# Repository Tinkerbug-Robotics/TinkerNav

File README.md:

# TinkerNav
RTK Rover and Base Station Firmware for TinkerNav Boards

For more information and boards go to: https://tinkerbugrobotics.com/

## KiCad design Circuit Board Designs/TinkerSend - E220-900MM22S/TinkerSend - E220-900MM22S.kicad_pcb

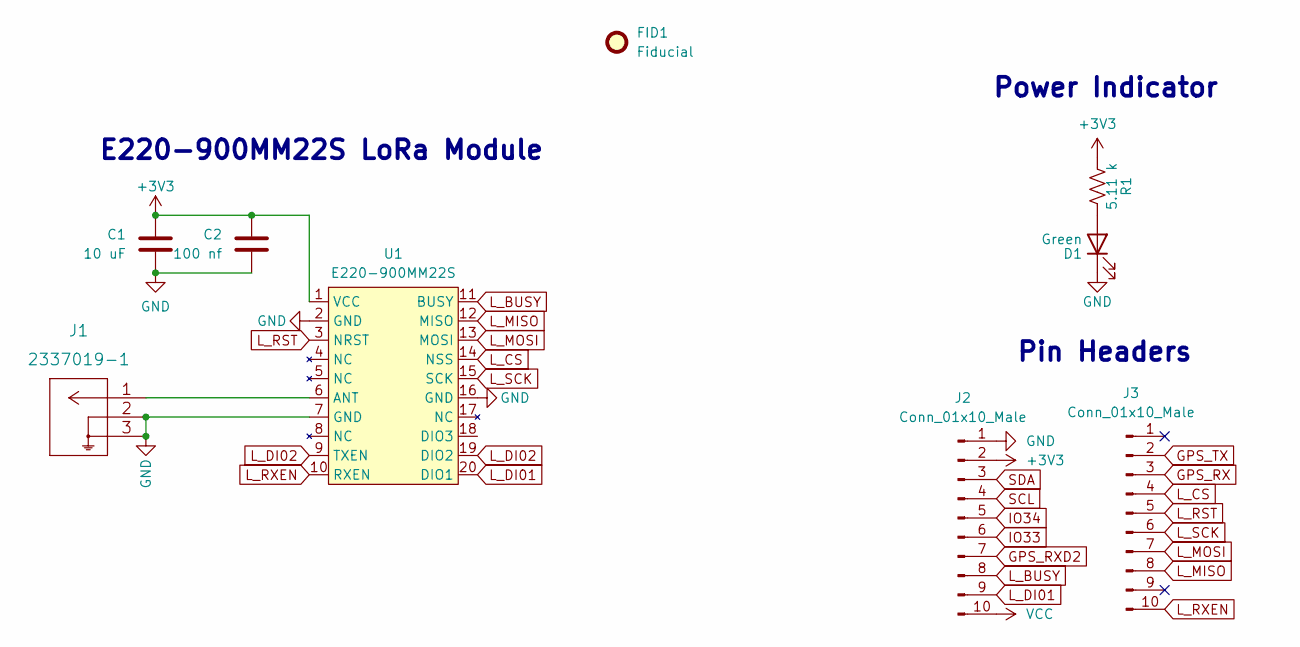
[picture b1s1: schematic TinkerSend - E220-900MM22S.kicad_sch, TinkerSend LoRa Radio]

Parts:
C1: 10 uF; C_0805_2012Metric
C2: 100 nf; C_0402_1005Metric
D1: Green; LED_0603_1608Metric
FID1: Fiducial; Fiducial_0.5mm_Mask1mm
J1: 2337019-1
J2, J3: Conn_01x10_Male; PinHeader_1x10_P2.54mm_Vertical
R1: 5.11 k; R_0603_1608Metric
U1: E220-900MM22S

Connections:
+3V3: C1.2, C2.2, J2.2, R1.2, U1.1 (VCC)
GND: C1.1, C2.1, D1.1 (K), J1.2, J1.3, J2.1, U1.2 (GND), U1.7 (GND), U1.16 (GND)
GPS_RX: J3.3
GPS_RXD2: J2.7
GPS_TX: J3.2
IO33: J2.6
IO34: J2.5
L_BUSY: J2.8, U1.11 (BUSY)
L_CS: J3.4, U1.14 (NSS)
L_DI01: J2.9, U1.20 (DIO1)
L_DI02: U1.9 (TXEN), U1.19 (DIO2)
L_MISO: J3.8, U1.12 (MISO)
L_MOSI: J3.7, U1.13 (MOSI)
L_RST: J3.5, U1.3 (NRST)
L_RXEN: J3.10, U1.10 (RXEN)
L_SCK: J3.6, U1.15 (SCK)
unnamed: D1.2 (A), R1.1
unnamed: J1.1, U1.6 (ANT)
SCL: J2.4
SDA: J2.3
VCC: J2.10

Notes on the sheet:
Power Indicator
Pin Headers
E220-900MM22S LoRa Module

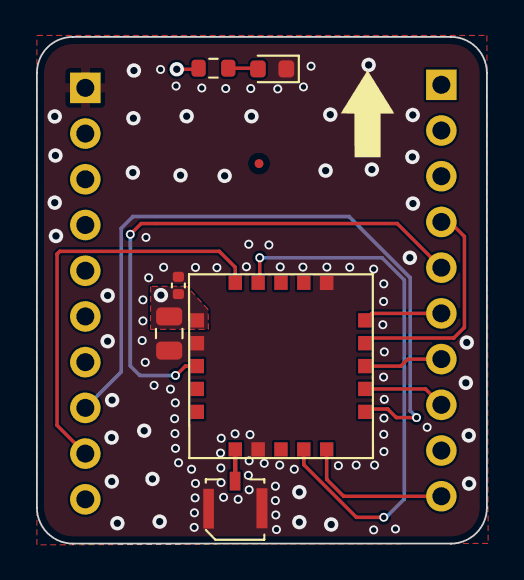
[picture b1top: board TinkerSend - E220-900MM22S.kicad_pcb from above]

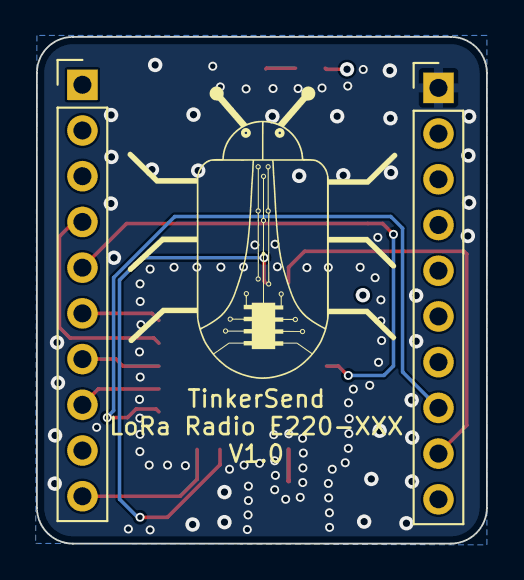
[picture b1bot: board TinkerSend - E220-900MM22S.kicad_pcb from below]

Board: 4 copper layers, 25.0 x 28.1 mm, 9 parts (2 on the bottom side), 13 nets.

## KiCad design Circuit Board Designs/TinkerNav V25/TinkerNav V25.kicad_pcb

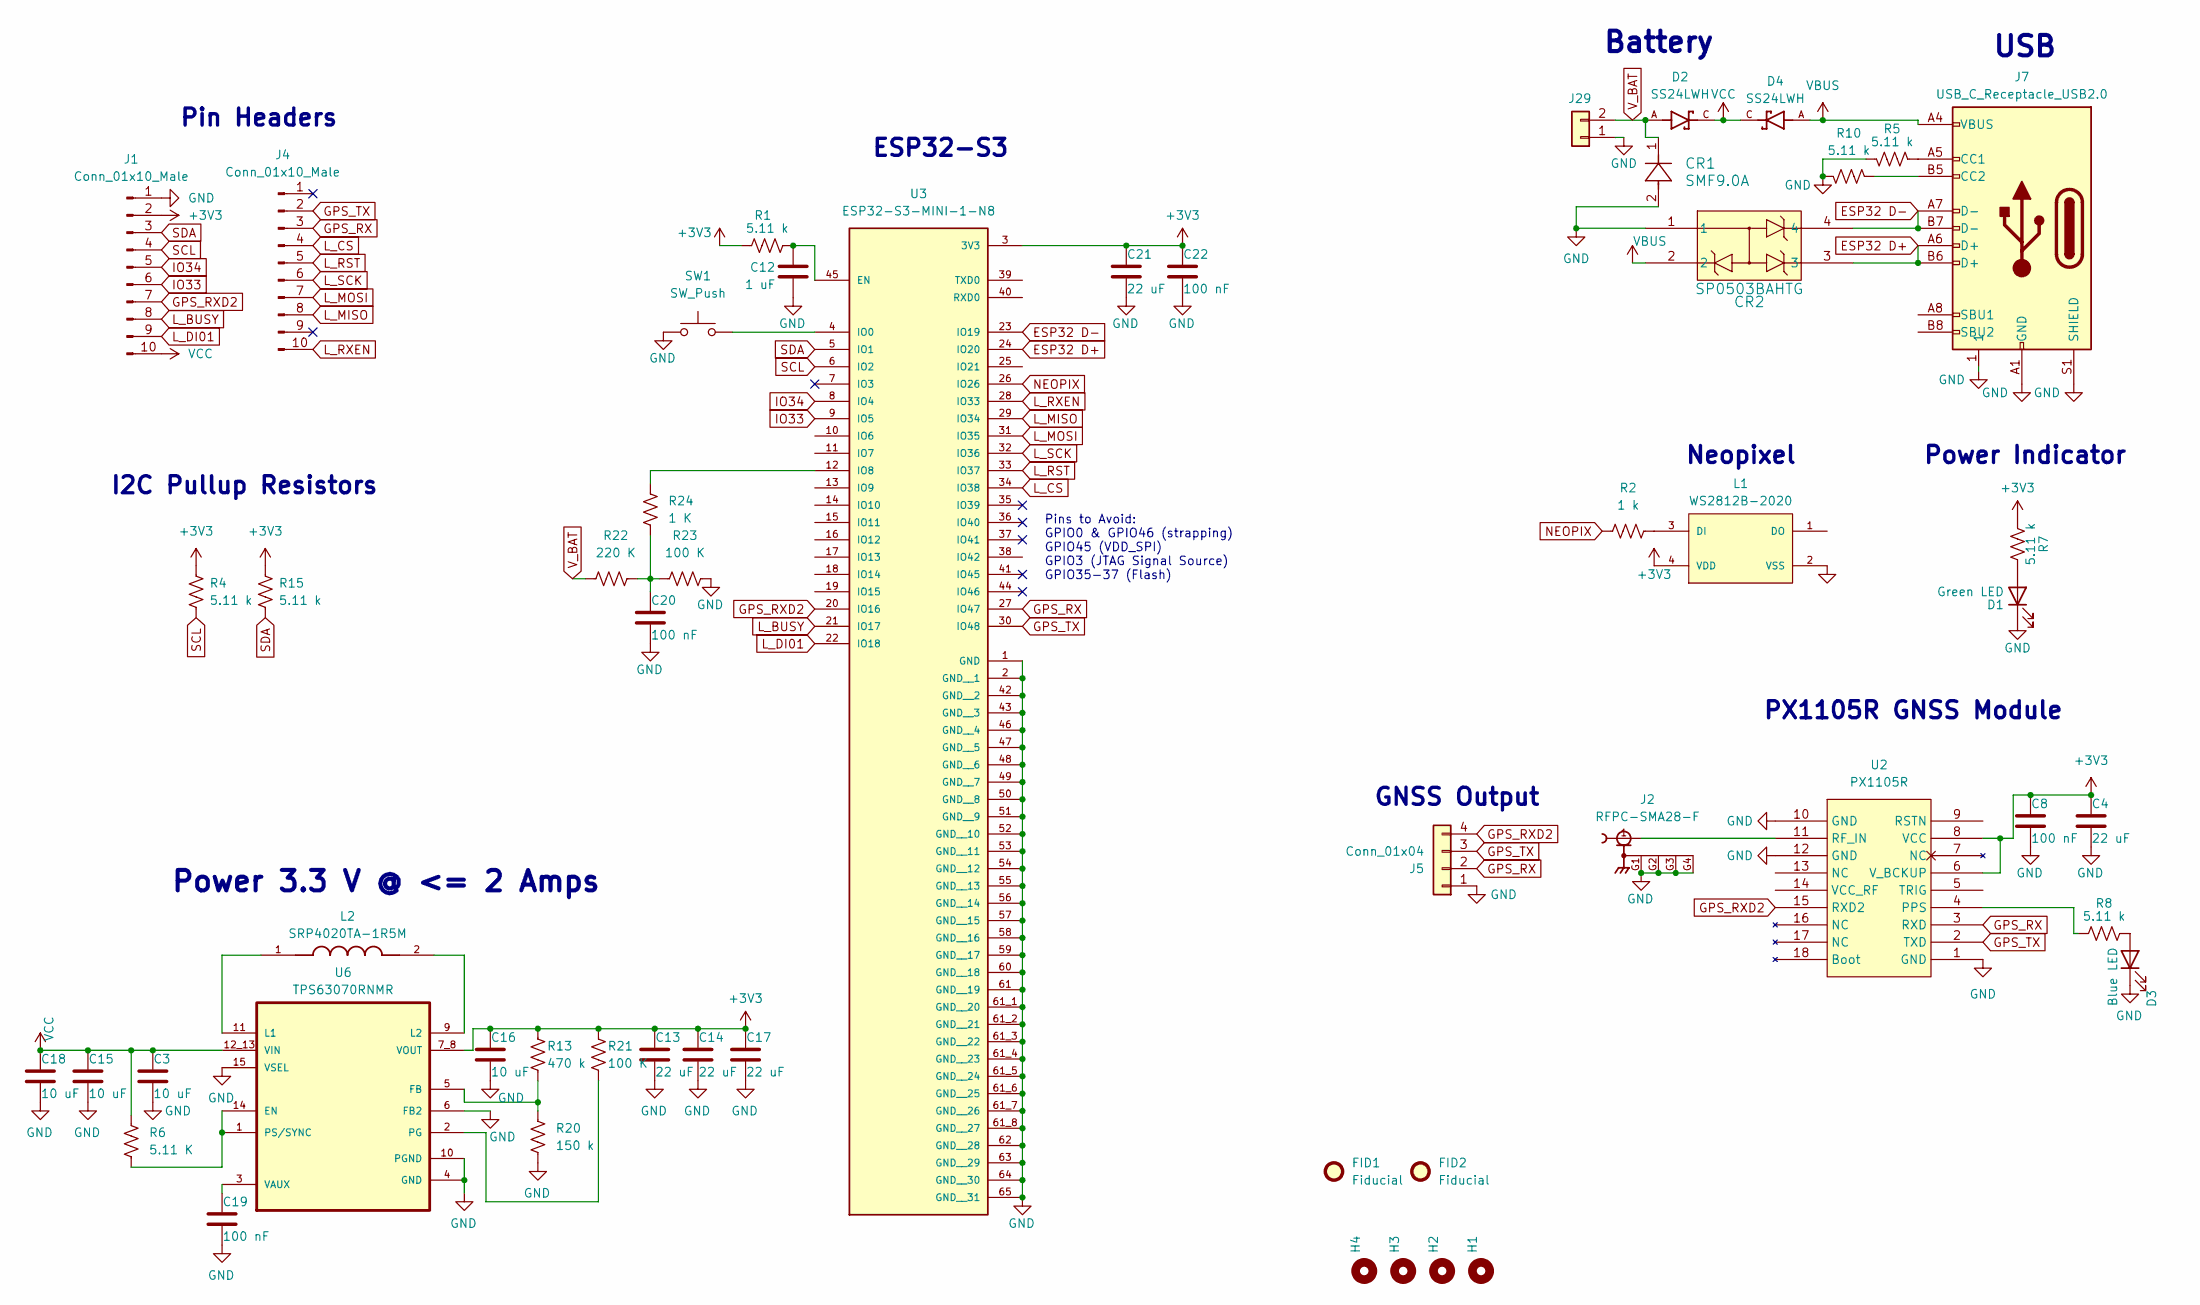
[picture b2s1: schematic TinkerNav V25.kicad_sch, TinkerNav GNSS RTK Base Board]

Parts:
C3, C16: 10 uF; C_0603_1608Metric
C4, C13, C14, C17, C21: 22 uF; C_0805_2012Metric
C8, C19, C20, C22: 100 nF; C_0603_1608Metric
C12: 1 uF; C_0603_1608Metric
C15, C18: 10 uF; C_0805_2012Metric
CR1: SMF9.0A; SMFSeries_LTF
CR2: SP0503BAHTG; TVS-SP05_LTF
D1: Green LED; LED_0603_1608Metric
D2, D4: SS24LWH; SODFL3718X102N; PARTREV C2103
D3: Blue LED; LED_0603_1608Metric
FID1, FID2: Fiducial; Fiducial_0.5mm_Mask1mm
H1, H2, H3, H4: MountingHole; MountingHole_2.2mm_M2_DIN965_Pad
J1, J4: Conn_01x10_Male; PinHeader_1x10_P2.54mm_Vertical
J2: RFPC-SMA28-F; GRADCONN_RFPC-SMA28-F; PARTREV 1.0
J5: Conn_01x04; JST_XH_B4B-XH-A_1x04_P2.50mm_Vertical
J7: USB_C_Receptacle_USB2.0; USB_C_Receptacle_HRO_TYPE-C-31-M-12
J29: Conn_01x02; JST_PH_B2B-PH-K_1x02_P2.00mm_Vertical
L1: WS2812B-2020; LED_WS2812B-2020_PLCC4_2.0x2.0mm; LCSC C965555
L2: SRP4020TA-1R5M; IND_SRP4020TA-1R5M
R1, R4, R5, R7, R8, R10, R15: 5.11 k; R_0603_1608Metric
R2: 1 k; R_0603_1608Metric
R6: 5.11 K; R_0603_1608Metric
R13: 470 k; R_0603_1608Metric
R20: 150 k; R_0603_1608Metric
R21, R23: 100 K; R_0603_1608Metric
R22: 220 K; R_0603_1608Metric
R24: 1 K; R_0603_1608Metric
SW1: SW_Push; R-667995_MIT
U2: PX1105R
U3: ESP32-S3-MINI-1-N8; XCVR_ESP32-S3-MINI-1-N8; PARTREV v0.6
U6: TPS63070RNMR; VREG_TPS63070RNMR

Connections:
+3V3: C4.1, C8.1, C13.1, C14.1, C16.1, C17.1, C21.1, C22.1, J1.2, L1.4 (VDD), R1.1, R4.2, R7.2, R13.2, R15.2, R21.2, U2.6 (V_BCKUP), U2.8 (VCC), U3.3 (3V3), U6.7_8 (VOUT)
ESP32 D+: CR2.3, J7.A6 (D+), J7.B6 (D+), U3.24 (IO20)
ESP32 D-: CR2.4, J7.A7 (D-), J7.B7 (D-), U3.23 (IO19)
GND: C3.2, C4.2, C8.2, C12.1, C13.2, C14.2, C15.2, C16.2, C17.2, C18.2, C19.2, C20.2, C21.2, C22.2, CR1.2, CR2.1, D1.1 (K), D3.1 (K), J1.1, J2.G1, J2.G2, J2.G3, J2.G4, J5.1, J7.1, J7.A1 (GND), J7.A12 (GND), J7.B1 (GND), J7.B12 (GND), J7.S1 (SHIELD), J29.1, L1.2 (VSS), R5.2, R10.2, R20.1, R23.2, SW1.1, U2.1 (GND), U2.10 (GND), U2.12 (GND), U3.1 (GND), U3.2 (GND__1), U3.42 (GND__2), U3.43 (GND__3), U3.46 (GND__4), U3.47 (GND__5), U3.48 (GND__6), U3.49 (GND__7), U3.50 (GND__8), U3.51 (GND__9), U3.52 (GND__10), U3.53 (GND__11), U3.54 (GND__12), U3.55 (GND__13), U3.56 (GND__14), U3.57 (GND__15), U3.58 (GND__16), U3.59 (GND__17), U3.60 (GND__18), U3.61 (GND__19), U3.61_1 (GND__20), U3.61_2 (GND__21), U3.61_3 (GND__22), U3.61_4 (GND__23), U3.61_5 (GND__24), U3.61_6 (GND__25), U3.61_7 (GND__26), U3.61_8 (GND__27), U3.62 (GND__28), U3.63 (GND__29), U3.64 (GND__30), U3.65 (GND__31), U6.4 (GND), U6.6 (FB2), U6.10 (PGND), U6.15 (VSEL)
GPS_RX: J4.3, J5.2, U2.3 (RXD), U3.27 (IO47)
GPS_RXD2: J1.7, J5.4, U2.15 (RXD2), U3.20 (IO16)
GPS_TX: J4.2, J5.3, U2.2 (TXD), U3.30 (IO48)
IO33: J1.6, U3.9 (IO5)
IO34: J1.5, U3.8 (IO4)
L_BUSY: J1.8, U3.21 (IO17)
L_CS: J4.4, U3.34 (IO38)
L_DI01: J1.9, U3.22 (IO18)
L_MISO: J4.8, U3.29 (IO34)
L_MOSI: J4.7, U3.31 (IO35)
L_RST: J4.5, U3.33 (IO37)
L_RXEN: J4.10, U3.28 (IO33)
L_SCK: J4.6, U3.32 (IO36)
NEOPIX: R2.1, U3.26 (IO26)
unnamed: C20.1, R22.2, R23.1, R24.1
unnamed: D1.2 (A), R7.1
unnamed: D3.2 (A), R8.2
unnamed: J7.A5 (CC1), R5.1
unnamed: J7.B5 (CC2), R10.1
unnamed: L1.3 (DI), R2.2
unnamed: R8.1, U2.4 (PPS)
unnamed: J2.1, U2.11 (RF_IN)
unnamed: C12.2, R1.2, U3.45 (EN)
unnamed: SW1.2, U3.4 (IO0)
unnamed: R24.2, U3.12 (IO8)
unnamed: R6.1, U6.1 (PS/SYNC), U6.14 (EN)
unnamed: R13.1, R20.2, U6.5 (FB)
unnamed: L2.1, U6.11 (L1)
unnamed: L2.2, U6.9 (L2)
unnamed: R21.1, U6.2 (PG)
unnamed: C19.1, U6.3 (VAUX)
SCL: J1.4, R4.1, U3.6 (IO2)
SDA: J1.3, R15.1, U3.5 (IO1)
VBUS: CR2.2, D4.A, J7.A4 (VBUS), J7.A9 (VBUS), J7.B4 (VBUS), J7.B9 (VBUS)
VCC: C3.1, C15.1, C18.1, D2.C, D4.C, J1.10, R6.2, U6.12_13 (VIN)
V_BAT: CR1.1, D2.A, J29.2, R22.1

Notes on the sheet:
Pins to Avoid: GPIO0 & GPIO46 (strapping) GPIO45 (VDD_SPI) GPIO3 (JTAG Signal Source) GPIO35-37 (Flash)
Battery
ESP32-S3
I2C Pullup Resistors
Pin Headers
Power Indicator
PX1105R GNSS Module
Neopixel
USB
Power 3.3 V @ <= 2 Amps
GNSS Output

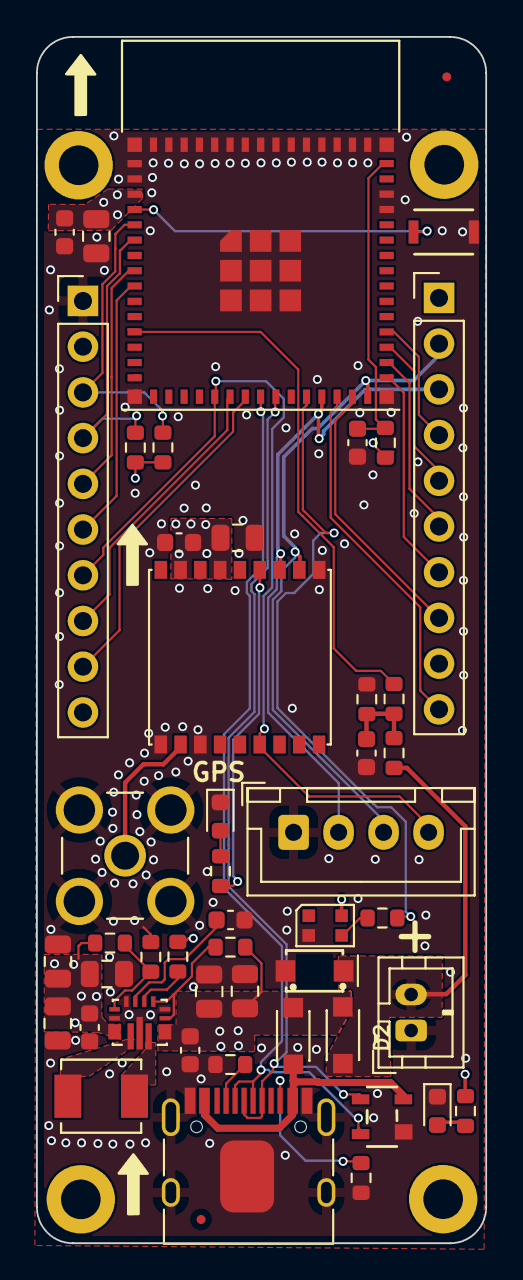
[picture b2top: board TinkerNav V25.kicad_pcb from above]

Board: 4 copper layers, 25.0 x 67.0 mm, 53 parts (0 on the bottom side), 40 nets.

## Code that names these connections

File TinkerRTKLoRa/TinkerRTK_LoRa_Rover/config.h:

#ifndef CONFIG_H
#define CONFIG_H

struct config 
{

    // Access point name and password
    inline static constexpr const char* AP_SSID = "tinkerbug_rover";
    inline static constexpr const char* AP_PASS = "Tinkerbug";

    // NMEA from SkyTraq
    static constexpr uint8_t GNSS_TX = 47;
    static constexpr uint8_t GNSS_RX = 48;
    static constexpr uint8_t GNSS_RXD2 = 16;

    // LoRa Radio (LLC68)
    static constexpr uint8_t  L_DIO1 = 18;
    static constexpr uint8_t  L_CS   = 38;
    static constexpr uint8_t  L_BUSY = 17;
    static constexpr uint8_t  L_RST  = 37;
    static constexpr uint8_t  L_MISO = 34;
    static constexpr uint8_t  L_MOSI = 35;
    static constexpr uint8_t  L_SCK  = 36;

    // Neopix LED driver pin
    static constexpr int NEO_PIN = 26;

    // LoRa Radio Configuration
    static constexpr float   FREQUENCY        = 905.0;
    static constexpr float   BANDWIDTH        = 250.0;
    static constexpr uint8_t SPREADING_FACTOR = 8;
    static constexpr uint8_t CODING_RATE      = 5;
    static constexpr uint8_t OUTPUT_POWER     = 22;
    static constexpr uint8_t PREAMBLE_LENGTH  = 12;

    // LoRa Data
    static constexpr int TX_QUEUE_SIZE = 8;
    static constexpr uint16_t MAX_RTCM_LENGTH = 2000;
    static constexpr int MAX_PACKET_LENGTH = 250;
    static constexpr size_t RTCM_BYTE_QUEUE_SIZE = 5000;
    static constexpr size_t RTCM_MSG_QUEUE_SIZE = 100;
    static const uint32_t STATUS_PERIOD_MS  = 2000;

    // Voltage reading
    static constexpr int VOLTAGE_PIN = 8;     // ADC input
    static constexpr float R1 = 220000.0;     // 220kΩ
    static constexpr float R2 = 100000.0;     // 100kΩ
    static constexpr float VREF = 3.3;        // ADC reference voltage
    static constexpr int ADC_MAX = 4095;      // 12-bit ADC on ESP32-S3

    // Battery type 
    static constexpr int NUM_BATTERY_CELLS = 2;

    // Power update period (ms)
    static constexpr int PWR_UPDATE_PERIOD_MS = 2000;

};

#endif // CONFIG_H

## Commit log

2026-01-09 Enhance battery cell configuration and SkyTraq setup
    Updated the TinkerRTK LoRa Base firmware to support dynamic battery cell count configuration and improved handling of SkyTraq GNSS settings. Added persistent storage for battery cell count and modifi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
2026-01-09 Update configuration for AP and GNSS pins
2026-01-09 Refactor battery cell count and radio setup
    Updated battery cell handling and radio initialization.
2026-01-09 Update GNSS and LoRa pin configurations
2026-01-09 Implement battery cell configuration in web UI
    Added battery cell configuration feature to the web UI.
2026-01-09 Update copyright year and add battery cell handling
2026-01-09 Add information link to README
    Added a link for more information about TinkerNav boards.

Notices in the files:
Circuit Board Designs/TinkerNav V25/TinkerNav V25.kicad_pcb:
License: Creative Commons: Attribution-ShareAlike
